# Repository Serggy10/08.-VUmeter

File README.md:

# Description
This project is based on the idea of a LED strip that reacts to sound. Controlled by an ESP32 and interacting with Alexa. Using a INMP441 microphone to capture the sound. Work in progress. Based on these ideas:

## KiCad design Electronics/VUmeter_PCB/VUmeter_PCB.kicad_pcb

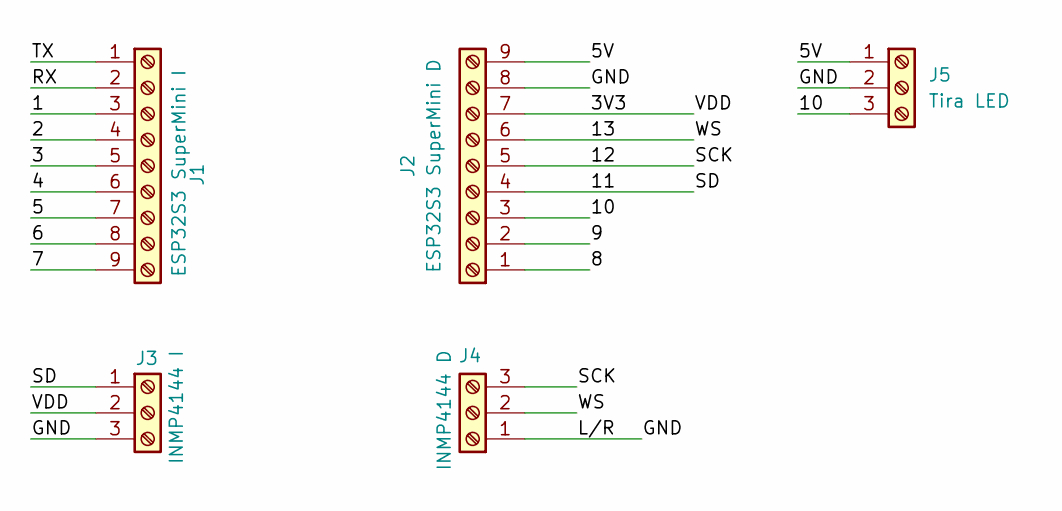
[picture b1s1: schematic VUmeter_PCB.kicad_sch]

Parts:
J1: ESP32S3 SuperMini I; PinHeader_1x09_P2.54mm_Vertical
J2: ESP32S3 SuperMini D; PinHeader_1x09_P2.54mm_Vertical
J3: INMP4144 I; PinHeader_1x03_P2.54mm_Vertical
J4: INMP4144 D; PinHeader_1x03_P2.54mm_Vertical
J5: Tira LED; PinHeader_1x03_P2.54mm_Vertical

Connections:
/1: J1.3
/2: J1.4
/3: J1.5
/3V3: J2.7, J3.2
/4: J1.6
/5: J1.7
/5V: J2.9, J5.1
/6: J1.8
/7: J1.9
/8: J2.1
/9: J2.2
/10: J2.3, J5.3
/11: J2.4, J3.1
/12: J2.5, J4.3
/13: J2.6, J4.2
/GND: J2.8, J3.3, J4.1, J5.2
/RX: J1.2
/TX: J1.1

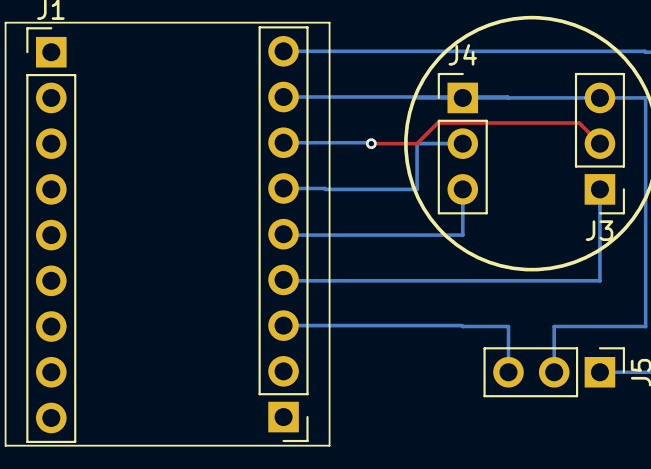
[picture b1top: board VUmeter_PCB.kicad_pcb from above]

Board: 2 copper layers, 5 parts (0 on the bottom side), 7 nets.

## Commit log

2025-03-06 Initial commit.
2025-03-06 Update commit.
2025-05-15 Box creation for PCB. Program update.
